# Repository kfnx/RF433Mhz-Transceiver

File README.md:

# RF433Mhz Simplex Transceiver
Simple data tranceiver Project using RF433MHz HC-12 and ATmega8535
Device can communicate with other same device using display and keypad like text messaging

Tools Used:
- ATmega8535
- RF433MHz HC-12
- 4x4 Keypad
- 2x16 LED Display
- Buzzer for notification

Schematic:

© 2016 Kafin Salim

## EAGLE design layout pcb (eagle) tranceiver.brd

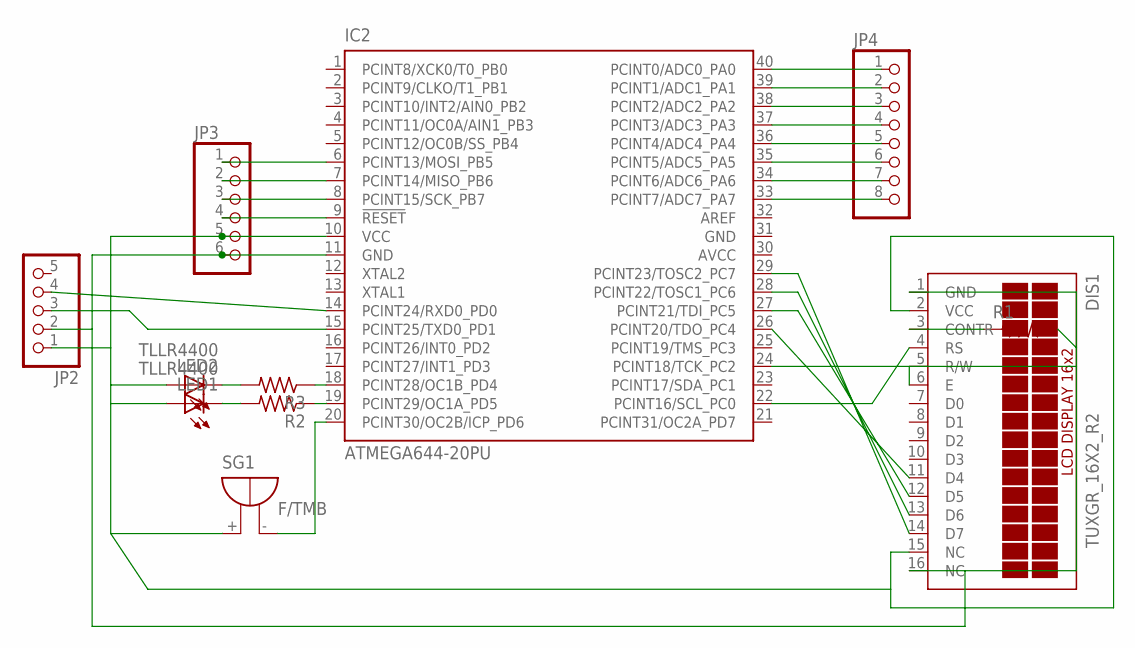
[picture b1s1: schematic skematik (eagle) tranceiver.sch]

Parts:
DIS1: TUXGR_16X2_R2
IC2: ATMEGA644-20PU; DIL40
JP2: PINHD-1X5; 1X05
JP3: PINHD-1X6; 1X06
JP4: PINHD-1X8; 1X08
LED1, LED2: TLLR4400; LED3MM
R1, R2, R3: R-US_VMTA55; VMTA55
SG1: F/TMB

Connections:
AVCC: IC2.30 (AVCC)
GND: IC2.31 (GND)
unnamed: DIS1.1 (GND), DIS1.5 (R/W), DIS1.16 (NC), IC2.11 (GND), JP2.2, JP3.6, R1.2
unnamed: DIS1.3 (CONTR), R1.1
unnamed: LED1.K (C), R2.2
unnamed: IC2.19 (PCINT29/OC1A_PD5), R2.1
unnamed: IC2.20 (PCINT30/OC2B/ICP_PD6), SG1.-
unnamed: DIS1.4 (RS), IC2.22 (PCINT16/SCL_PC0)
unnamed: IC2.9 (!RESET), JP3.4
unnamed: IC2.8 (PCINT15/SCK_PB7), JP3.3
unnamed: IC2.7 (PCINT14/MISO_PB6), JP3.2
unnamed: IC2.6 (PCINT13/MOSI_PB5), JP3.1
unnamed: DIS1.2 (VCC), DIS1.15 (NC), IC2.10 (VCC), JP2.1, JP3.5, LED1.A, LED2.A, SG1.+
unnamed: IC2.15 (PCINT25/TXD0_PD1), JP2.3
unnamed: IC2.40 (PCINT0/ADC0_PA0), JP4.1
unnamed: IC2.14 (PCINT24/RXD0_PD0), JP2.4
unnamed: IC2.39 (PCINT1/ADC1_PA1), JP4.2
unnamed: DIS1.6 (E), IC2.24 (PCINT18/TCK_PC2)
unnamed: DIS1.11 (D4), IC2.26 (PCINT20/TDO_PC4)
unnamed: DIS1.12 (D5), IC2.27 (PCINT21/TDI_PC5)
unnamed: DIS1.13 (D6), IC2.28 (PCINT22/TOSC1_PC6)
unnamed: DIS1.14 (D7), IC2.29 (PCINT23/TOSC2_PC7)
unnamed: LED2.K (C), R3.2
unnamed: IC2.18 (PCINT28/OC1B_PD4), R3.1
unnamed: IC2.38 (PCINT2/ADC2_PA2), JP4.3
unnamed: IC2.37 (PCINT3/ADC3_PA3), JP4.4
unnamed: IC2.36 (PCINT4/ADC4_PA4), JP4.5
unnamed: IC2.35 (PCINT5/ADC5_PA5), JP4.6
unnamed: IC2.34 (PCINT6/ADC6_PA6), JP4.7
unnamed: IC2.33 (PCINT7/ADC7_PA7), JP4.8

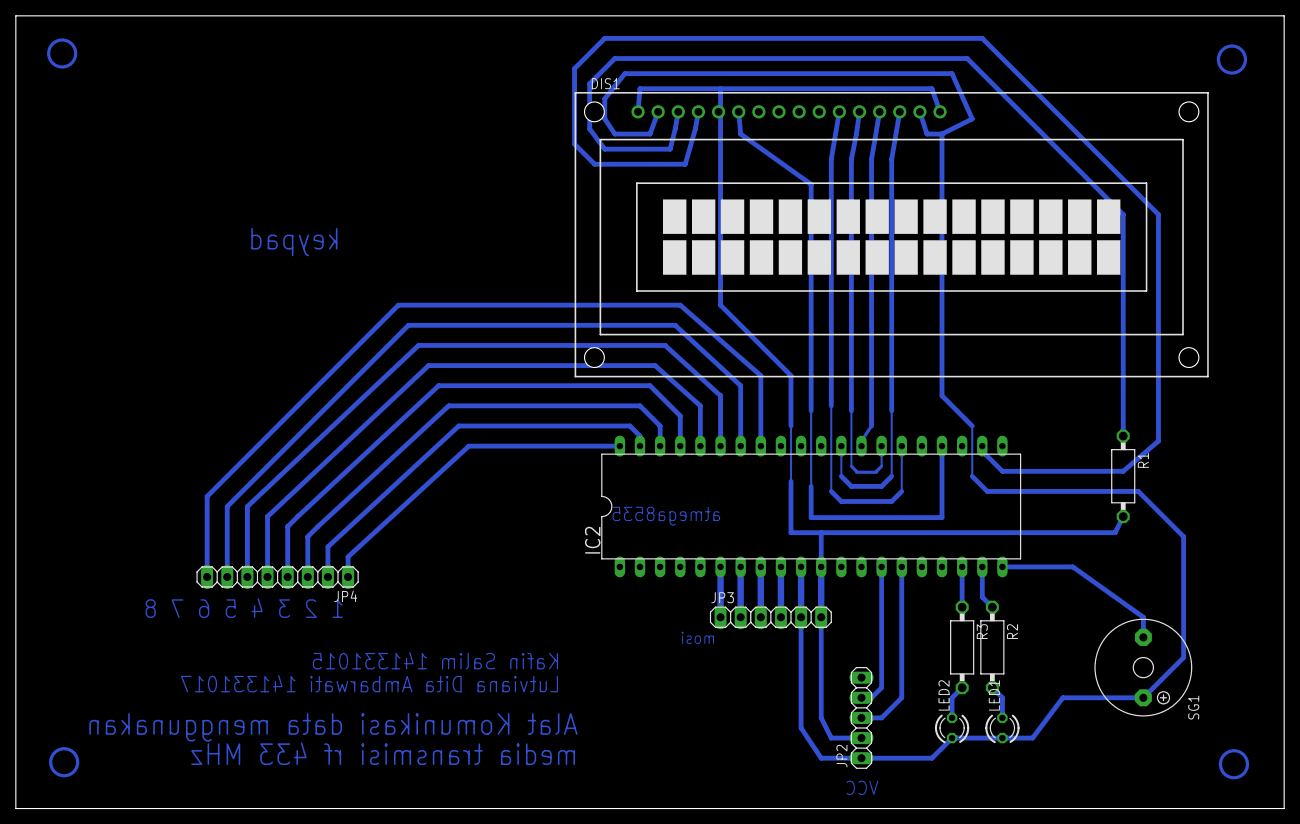
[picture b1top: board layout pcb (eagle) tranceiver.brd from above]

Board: 2 copper layers, 160.0 x 100.0 mm, 11 parts (0 on the bottom side), 28 nets.

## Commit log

2019-02-11 Create LICENSE
